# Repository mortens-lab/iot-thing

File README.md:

# iot-thing
Universal iot device based on an ESP32 WROOM module

KiCad 7.0 files for device

Link to YouTube video : (https://youtu.be/b-7bMl6fJio)

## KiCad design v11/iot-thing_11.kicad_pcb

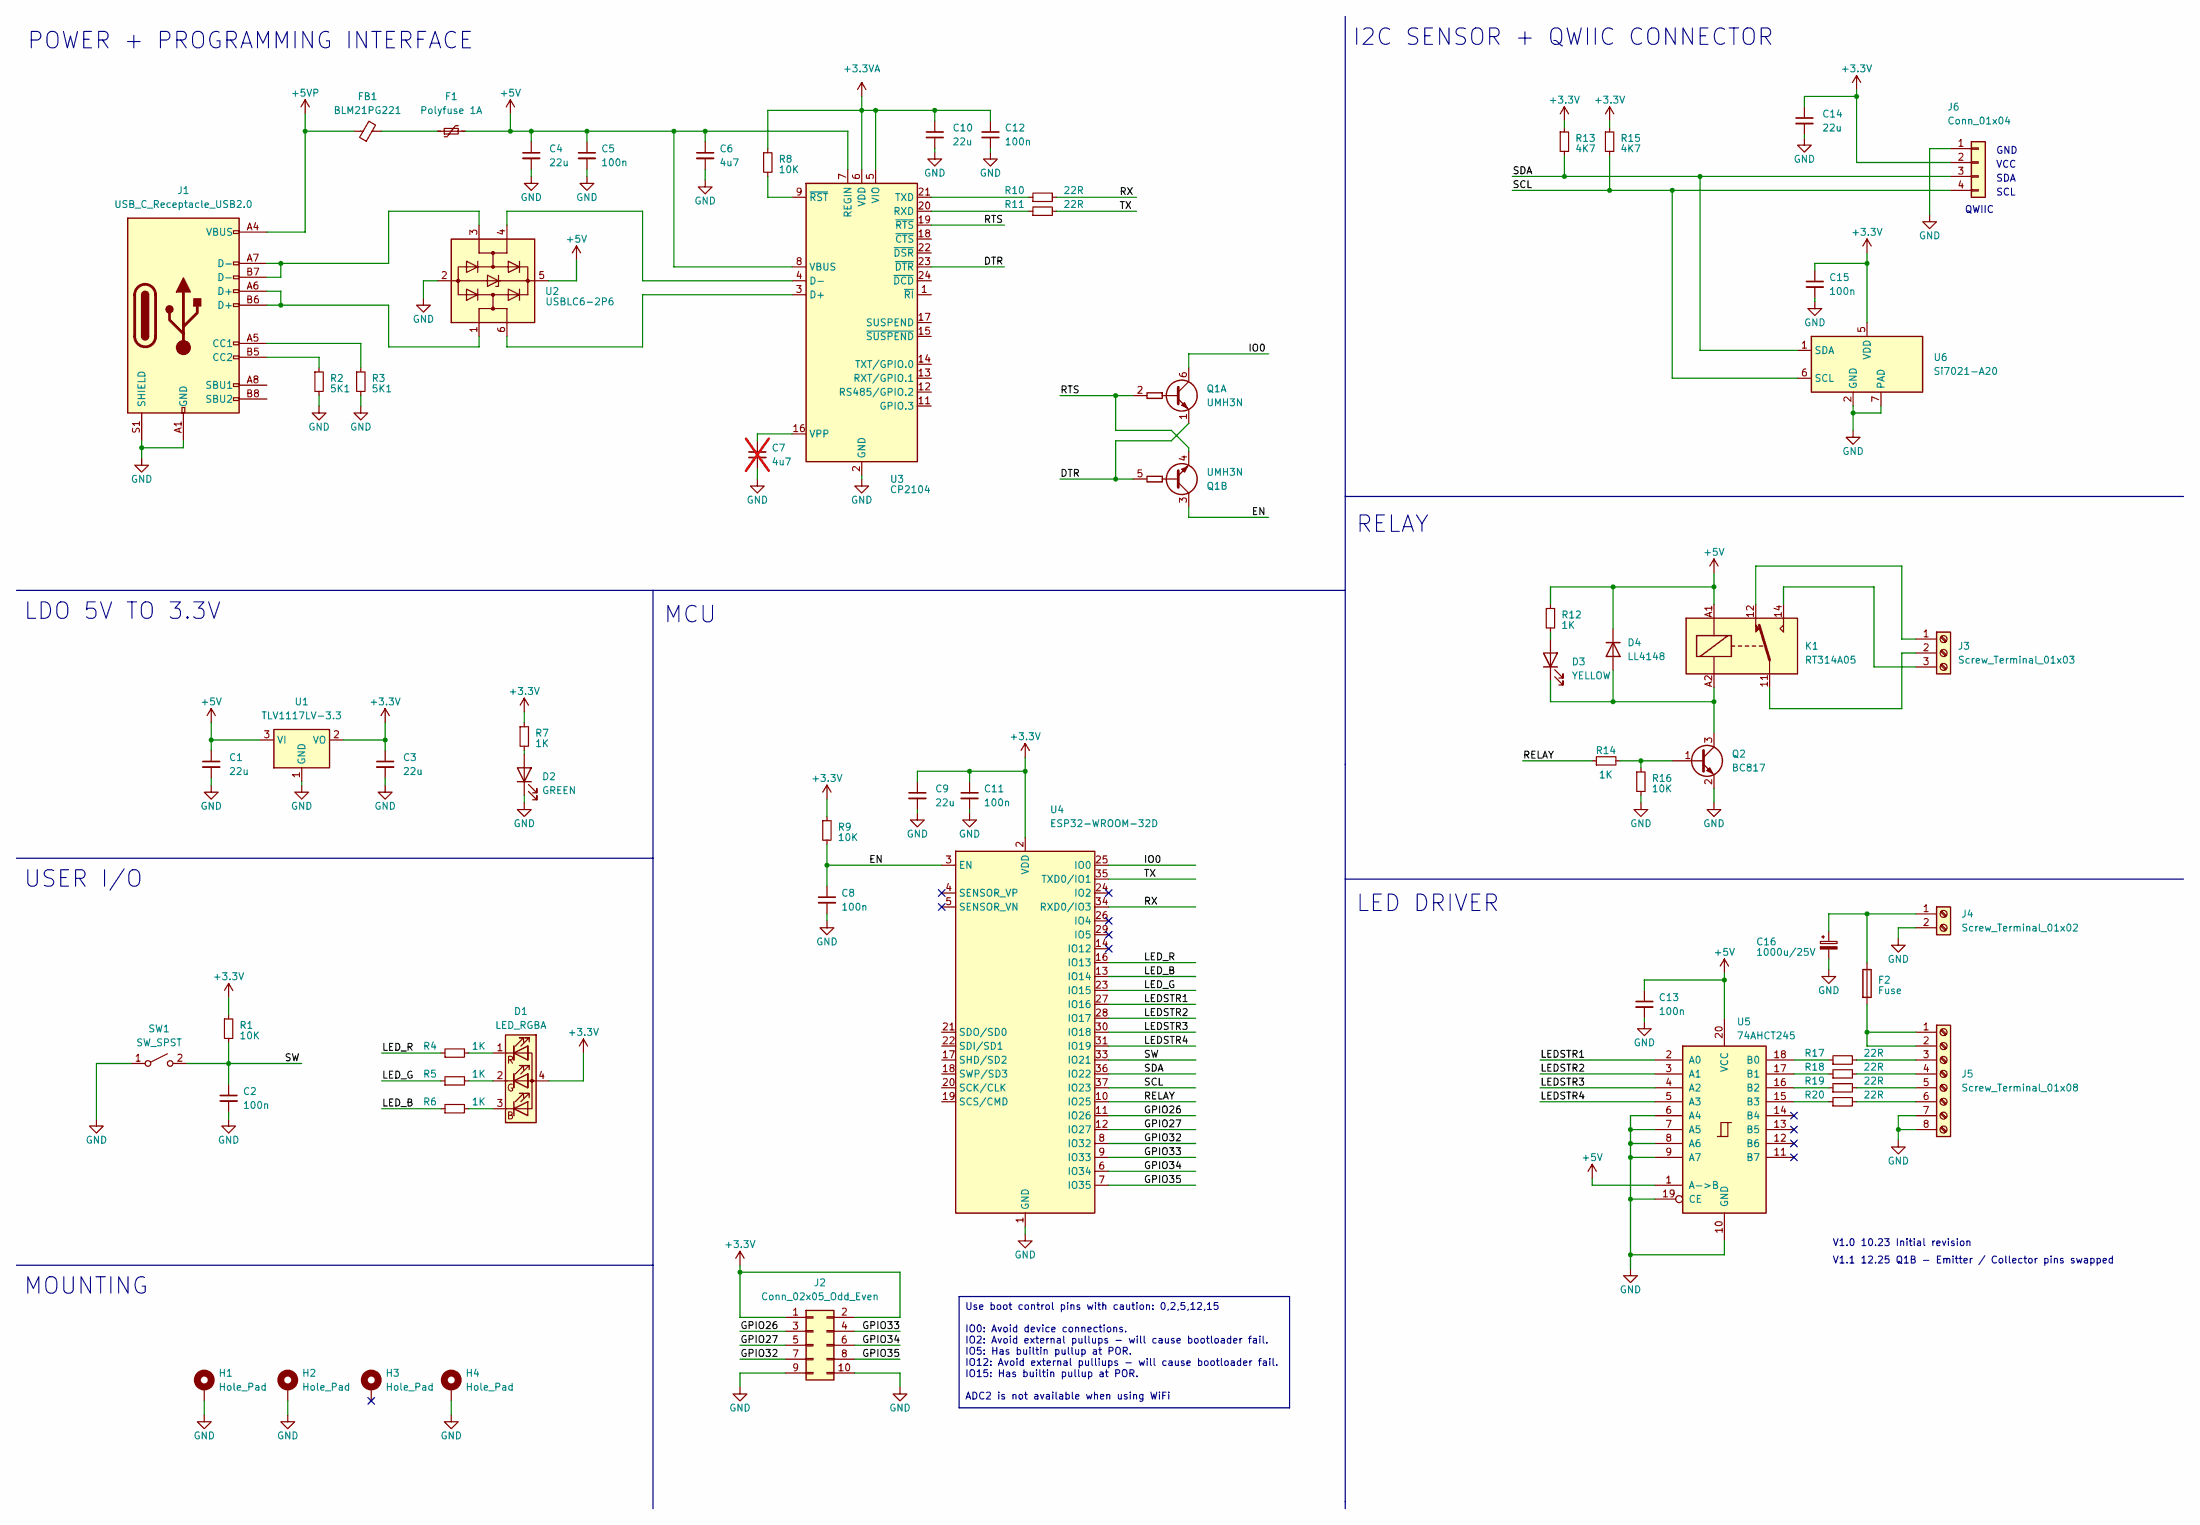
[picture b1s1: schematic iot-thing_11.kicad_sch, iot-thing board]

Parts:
C1, C3, C4, C9, C10, C14: 22u; C_0805_2012Metric_Pad1.18x1.45mm_HandSolder
C2, C5, C8, C11, C12, C13, C15: 100n; C_0402_1005Metric_Pad0.74x0.62mm_HandSolder
C6: 4u7; C_0805_2012Metric_Pad1.18x1.45mm_HandSolder
C7: 4u7; C_0805_2012Metric_Pad1.18x1.45mm_HandSolder; not fitted
C16: 1000u/25V; CP_Radial_D10.0mm_P5.00mm
D1: LED_RGBA; LED_RGB_Wuerth-PLCC4_3.2x2.8mm_150141M173100
D2: GREEN; LED_0603_1608Metric_Pad1.05x0.95mm_HandSolder
D3: YELLOW; LED_0603_1608Metric_Pad1.05x0.95mm_HandSolder
D4: LL4148; D_MiniMELF
F1: Polyfuse 1A; Fuse_1206_3216Metric_Pad1.42x1.75mm_HandSolder
F2: Fuse; FUSE_696105003002
FB1: BLM21PG221; L_0603_1608Metric_Pad1.05x0.95mm_HandSolder
H1, H2, H4: Hole_Pad; MountingHole_3.2mm_M3_Pad_Via
H3: Hole_Pad; MountingHole_3.2mm_M3_DIN965
J1: USB_C_Receptacle_USB2.0; USB_C_Receptacle_HRO_TYPE-C-31-M-12
J2: Conn_02x05_Odd_Even; PinHeader_2x05_P2.54mm_Vertical
J3: Screw_Terminal_01x03; TerminalBlock_Phoenix_MKDS-3-3-5.08_1x03_P5.08mm_Horizontal
J4: Screw_Terminal_01x02; TerminalBlock_Phoenix_MKDS-1,5-2-5.08_1x02_P5.08mm_Horizont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
J5: Screw_Terminal_01x08; TerminalBlock_Phoenix_MKDS-1,5-8_1x08_P5.00mm_Horizontal
J6: Conn_01x04; JST_SH_SM04B-SRSS-TB_1x04-1MP_P1.00mm_Horizontal
K1: RT314A05; Relay_SPDT_Schrack-RT1-16A-FormC_RM5mm
Q1: UMH3N; SOT-363_SC-70-6
Q2: BC817; SOT-23
R1, R8, R9, R16: 10K; R_0402_1005Metric_Pad0.72x0.64mm_HandSolder
R2, R3: 5K1; R_0402_1005Metric_Pad0.72x0.64mm_HandSolder
R4, R5, R6, R7, R12, R14: 1K; R_0402_1005Metric_Pad0.72x0.64mm_HandSolder
R10, R11, R17, R18, R19, R20: 22R; R_0402_1005Metric_Pad0.72x0.64mm_HandSolder
R13, R15: 4K7; R_0402_1005Metric_Pad0.72x0.64mm_HandSolder
SW1: SW_SPST; SW_Push_1P1T_NO_6x6mm_H9.5mm
U1: TLV1117LV-3.3; SOT-223-3_TabPin2
U2: USBLC6-2P6; SOT-666
U3: CP2104; QFN-24-1EP_4x4mm_P0.5mm_EP2.6x2.6mm
U4: ESP32-WROOM-32D
U5: 74AHCT245; DIP-20_W7.62mm
U6: Si7021-A20; DFN-6-1EP_3x3mm_P1mm_EP1.5x2.4mm

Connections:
+3.3V: C3.1, C9.1, C11.1, C14.1, C15.1, D1.4 (A), J2.1, J2.2, J6.2, R1.1, R7.1, R9.1, R13.1, R15.1, U1.2 (VO), U4.2 (VDD), U6.5 (VDD)
+3.3VA: C10.1, C12.1, R8.1, U3.5 (VIO), U3.6 (VDD)
+5V: C1.1, C4.1, C5.1, C6.1, C13.1, D4.1 (K), F1.2, K1.A1, R12.1, U1.3 (VI), U2.5 (VBUS), U3.7 (REGIN), U3.8 (VBUS), U5.1 (A->B), U5.20 (VCC)
+5VP: FB1.1, J1.A4 (VBUS), J1.A9 (VBUS), J1.B4 (VBUS), J1.B9 (VBUS)
/DTR: Q1.1 (E1), Q1.5 (B2), U3.23 (~DTR)
/EN: C8.1, Q1.3 (C2), R9.2, U4.3 (EN)
/GPIO26: J2.3, U4.11 (IO26)
/GPIO27: J2.5, U4.12 (IO27)
/GPIO32: J2.7, U4.8 (IO32)
/GPIO33: J2.4, U4.9 (IO33)
/GPIO34: J2.6, U4.6 (IO34)
/GPIO35: J2.8, U4.7 (IO35)
/IO0: Q1.6 (C1), U4.25 (IO0)
/LEDSTR1: U4.27 (IO16), U5.2 (A0)
/LEDSTR2: U4.28 (IO17), U5.3 (A1)
/LEDSTR3: U4.30 (IO18), U5.4 (A2)
/LEDSTR4: U4.31 (IO19), U5.5 (A3)
/LED_B: R6.1, U4.13 (IO14)
/LED_G: R5.1, U4.23 (IO15)
/LED_R: R4.1, U4.16 (IO13)
/RELAY: R14.1, U4.10 (IO25)
/RTS: Q1.2 (B1), Q1.4 (E2), U3.19 (~RTS)
/RX: R10.2, U4.34 (RXD0/IO3)
/SCL: J6.4, R15.2, U4.37 (IO23), U6.6 (SCL)
/SDA: J6.3, R13.2, U4.36 (IO22), U6.1 (SDA)
/SW: C2.1, R1.2, SW1.2 (B), U4.33 (IO21)
/TX: R11.2, U4.35 (TXD0/IO1)
GND: C1.2, C2.2, C3.2, C4.2, C5.2, C6.2, C7.2, C8.2, C9.2, C10.2, C11.2, C12.2, C13.2, C14.2, C15.2, C16.2, D2.1 (K), H1.1, H2.1, H4.1, J1.A1 (GND), J1.A12 (GND), J1.B1 (GND), J1.B12 (GND), J1.S1 (SHIELD), J2.9, J2.10, J4.2, J5.7, J5.8, J6.1, Q2.2 (E), R2.2, R3.2, R16.2, SW1.1 (A), U1.1 (GND), U2.2 (GND), U3.2 (GND), U3.25 (GND), U4.1 (GND), U4.15 (GND), U4.38 (GND), U4.39 (GND), U5.6 (A4), U5.7 (A5), U5.8 (A6), U5.9 (A7), U5.10 (GND), U5.19 (CE), U6.2 (GND), U6.7 (PAD)
unnamed: D1.3 (BK), R6.2
unnamed: D1.2 (GK), R5.2
unnamed: D1.1 (RK), R4.2
unnamed: D2.2 (A), R7.2
unnamed: D3.2 (A), R12.2
unnamed: D3.1 (K), D4.2 (A), K1.A2, Q2.3 (C)
unnamed: F1.1, FB1.2
unnamed: J1.A5 (CC1), R3.1
unnamed: J1.B5 (CC2), R2.1
unnamed: J1.A6 (D+), J1.B6 (D+), U2.1 (I/O1)
unnamed: J1.A7 (D-), J1.B7 (D-), U2.3 (I/O2)
unnamed: J3.1, K1.12
unnamed: J3.2, K1.11
unnamed: J3.3, K1.14
unnamed: C16.1, F2.1, J4.1
unnamed: F2.2, J5.1, J5.2
unnamed: J5.3, R17.2
unnamed: J5.4, R18.2
unnamed: J5.5, R19.2
unnamed: J5.6, R20.2
unnamed: Q2.1 (B), R14.2, R16.1
unnamed: U2.6 (I/O1), U3.3 (D+)
unnamed: U2.4 (I/O2), U3.4 (D-)
unnamed: R11.1, U3.20 (RXD)
unnamed: R10.1, U3.21 (TXD)
unnamed: C7.1, U3.16 (VPP)
unnamed: R8.2, U3.9 (~RST)
unnamed: R17.1, U5.18 (B0)
unnamed: R18.1, U5.17 (B1)
unnamed: R19.1, U5.16 (B2)
unnamed: R20.1, U5.15 (B3)

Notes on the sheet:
Use boot control pins with caution: 0,2,5,12,15 IO0: Avoid device connections. IO2: Avoid external pullups - will cause bootloader fail. IO5: Has builtin pullup at POR. IO12: Avoid external pulliups - will cause bootloader fail. IO15: Has builtin pullup at POR. ADC2 is not available when using WiFi
LDO 5V TO 3.3V
MOUNTING
GND
SCL
SDA
V1.1 12.25 Q1B - Emitter / Collector pins swapped
I2C SENSOR + QWIIC CONNECTOR
V1.0 10.23 Initial revision
USER I/O
RELAY
MCU
QWIIC
LED DRIVER
POWER + PROGRAMMING INTERFACE
VCC

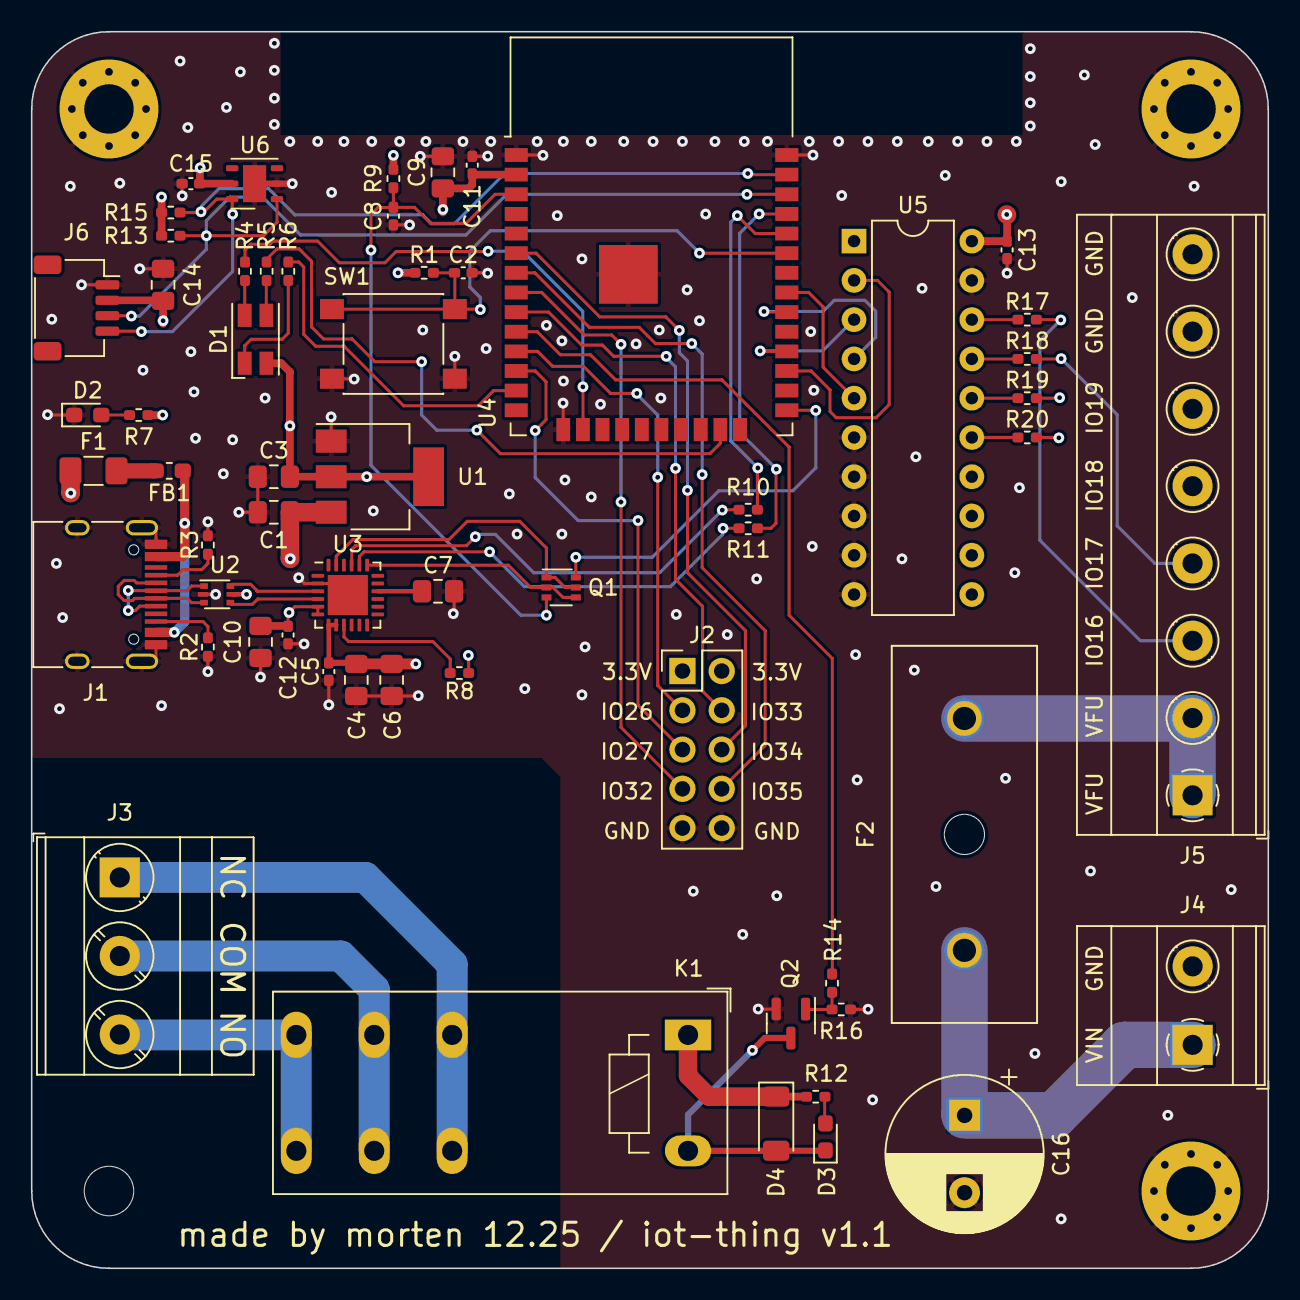
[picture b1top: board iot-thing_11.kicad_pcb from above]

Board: 4 copper layers, 80.0 x 80.0 mm, 63 parts (0 on the bottom side), 59 nets.

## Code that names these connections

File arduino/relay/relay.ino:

#define SDA     22 
#define SCL     23 
#define LED_R   15
#define LED_G   14
#define LED_B   13
#define RELAY   25
#define LEDSTR1 16
#define LEDSTR2 17
#define LEDSTR3 18
#define LEDSTR4 19
#define SW      21
#define GPIO26  26
#define GPIO27  27
#define GPIO32  32
#define GPIO33  33
#define GPIO34  34
#define GPIO35  35


void setup() 
{
  pinMode(RELAY, OUTPUT);
  pinMode(SW, INPUT);
  pinMode(LED_R, OUTPUT);
  pinMode(LED_G, OUTPUT);
  pinMode(LED_B, OUTPUT);
  digitalWrite(RELAY, LOW);  
  digitalWrite(LED_R, HIGH);  
  digitalWrite(LED_G, HIGH);  
  digitalWrite(LED_B, HIGH);  
  delay(1000);
  digitalWrite(LED_R, LOW);    // RED
  delay(1000);
  digitalWrite(LED_R, HIGH);  
  delay(300);
  digitalWrite(LED_G, LOW);    // GREEN
  delay(1000);
  digitalWrite(LED_G, HIGH);  
  delay(300);
  digitalWrite(LED_B, LOW);    // BLUE
  delay(1000);
  digitalWrite(LED_B, HIGH);  
  delay(300);
}


void loop() 
{
  if (digitalRead(SW)==1)
  {
    digitalWrite(RELAY, LOW);  
    digitalWrite(LED_R, HIGH);  
  }
  else
  {
    digitalWrite(RELAY, HIGH);  
    digitalWrite(LED_R, LOW);  
  }
}

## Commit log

2024-01-09 Create LICENSE
